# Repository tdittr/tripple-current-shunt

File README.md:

# Tripple Current Shunt

This is a small PCB project to measure current consumption and voltages in a multi battery camper van environment.

To do this it hosts three [INA219](https://www.ti.com/product/INA219) power monitors,
one [ADS1015](https://www.ti.com/product/ADS1015) four channel ADC to measure ground offsets,
one [MCP9808](https://www.microchip.com/en-us/product/MCP9808) temperature sensor and
a [M24C02](https://www.st.com/en/memories/m24c02-r.html) EEPROM to store calibration data.

## Interfaces

The board has three different interfaces. A [I2C](#i2c) digital interface for reading the measurements.
Three [Current Inputs](#current-input)
to measure the current flows into and out of the batteries. Three [Voltage Inputs](#voltage-input) to measure the ground
offset of the batteries.

### I2C

The I2C interface is wired to two JST-PH connectors with a pin-out compatible
to [Adafruits Stemma](https://learn.adafruit.com/introducing-adafruit-stemma-qt/technical-specs) connection. The
footprint also fits the connector and pin-out
of [Seedstudios Grove System](https://wiki.seeedstudio.com/Grove_System/#grove-i2c). The two connectors are wired in
parallel to allow for daisy-chaining. The power is also supplied via this connector (from rev2 onwards).

**Note on using Grove Connectors:** The 90 degree version of the grove connector seem to count their pins from right to
left - so inverse to how JST counts their pins. To use the Grove connectors you can either mount them on the backside of
the board or use the upright connectors with the clip facing to the edge of the board.

#### I2C Addresses

The six I2C slaves on the board are configured to follow a schema where the lowest two bits of the address are defined
per board. This allows usage of up to four boards with a total of 12 channels on a single bus. The individual addresses
are listed below. *xx* marks the bits set via jumpers (see screenshot below).

| Device      | Address Pattern | Board 0 | Board 1 | Board 2 | Board 3 |
|-------------|-----------------|---------|---------|---------|---------|
| MCP9808     | 0b001_10*xx*    | 0x18    | 0x19    | 0x1a    | 0x1b    |
| INA219 Ch A | 0b100_00*xx*    | 0x40    | 0x41    | 0x42    | 0x43    |
| INA219 Ch B | 0b100_01*xx*    | 0x44    | 0x45    | 0x46    | 0x47    |
| ADS1015     | 0b100_10*xx*    | 0x48    | 0x49    | 0x4a    | 0x4b    |
| INA219 Ch C | 0b100_11*xx*    | 0x4c    | 0x4d    | 0x4e    | 0x4f    |
| M24C02      | 0b101_00*xx*    | 0x50    | 0x51    | 0x52    | 0x53    |

|                                                                                                                                      |
|--------------------------------------------------------------------------------------------------------------------------------------------------------------------------------------------------------|
| There should always be one of JP1, JP2, JP3 or JP4 closed. Then close JP11 or JP12 when the matching box is filled. To select for example the address *10* for the board you would close JP3 and JP12. |

### Current Input

The current inputs are connected inline between the batteries and the consumers. They can be connected using
either [Wago 2604-1103 terminal blocks](https://www.wago.com/global/pcb-terminal-blocks-and-pluggable-connectors/pcb-terminal-block/p/2604-1103)
or a single row terminal block with 5mm pin spacing.

The board offers the option to place a [miniOTO fuse holder](https://imaxx.nl/product/minioto-holder-h7810/) in line to
protect the board and connections.

The current is then converted to a voltage using a current shunt. The different options for this are described
in ["Choosing a Shunt Resistor"](#choosing-a-shunt-resistor).

### Voltage Input

To measure the voltage offset between the board ground and the battery ground the connector used for
the [Current Input](#current-input) offers an extra connection. The input can tolerate a maximum voltage of ±20V but can
only measure about a ±5V offset. This can easily be adapted to other needs,
see [Adapting Voltage Dividers](#adapting-voltage-dividers).

## Design considerations

The board is designed to be easily adaptable to different situations. The easiest adaptions are to just leave parts out:

* Remove the fuse holders (e.g. because you already have a fuse box), and bridge that footprint
* Remove the temperature sensor and/or EEPROM to save cost
* Remove the EMI filter by not populating the capacitors and bridging the ferrite-beads

For the more complex considerations see below:

### Choosing a Shunt Resistor

**1. Choosing a footprint:** The board offers four different footprints for the shunt resistors:

* Single-Inline 4-pin through-hole
  for [Isabellenhütte PBV](https://www.isabellenhuette.de/fileadmin/user_upload/PBV.PDF) resistors
* SMD 2512 resistors
* SMD 1206 resistors
* Off-Board Shunt like [Vishay RTOP](https://www.vishay.com/product/50045/)

When using any other resistor footprint then the Single-Inline one the two jumpers next to the resistor footprints needs
to be closed. This connects the voltage sense terminals to the current terminals.

The screenshot shows the resistor footprints for channel A. R5 is for the *Single-Inline 4-pin through-hole* and R2 for
either SMD 2512 or SMD 1206. To use an external shunt do not populate any of the two. If you want to use any shunt that
is not the Single-Inline 4-pin close the two jumpers below R2.

**2. Check maximum values:** Calculate the maximum resistor value for a given current and power rating:

$R \leq \frac{P}{I^2}$

**3. Check voltage over shunt:** The INA219 can work with up to 26V but can measure a either ±40mV, ±80mV, ±160mV or
±320mV of shunt voltage. Using a lower shunt voltage will give a lower power loss on the shunt while aiming for a higher
shunt voltage increases signal-to-noise ratio.
You can calculate the voltage over the shunt by $U_{shunt}=R_{shunt} \cdot I$.

**Note:** Check whether the trace width is sufficient for your current. You can add extra solder and copper to the
traces on the bottom side to improve the current capabilities.

### Adapting Voltage Dividers

The voltage dividers for the ground offset are set to allow for ±5V input. This is achieved by building a voltage
divider between the input voltage and 5V. The output voltage can then be calculated by:

$U_{out} = \frac{5V + U_{in}}{2}$

There are however footprints to form a voltage divider between the input and ground. So it could be used to measure
another bus voltage.

**Note:** When adapting this take care to not overload the clamping diodes or the resistors in the voltage divider.

### Adapting Low Pass Filters

The current and voltage inputs host capacitors to form RC low-pass filters. The calculations for these can be found in
the schematic.

# License

Licensed under the CERN Open Hardware Licence Version 2 - Permissive.
Unless you explicitly state otherwise, any contribution intentionally submitted by you, shall be licensed as above,
without any additional terms or conditions.

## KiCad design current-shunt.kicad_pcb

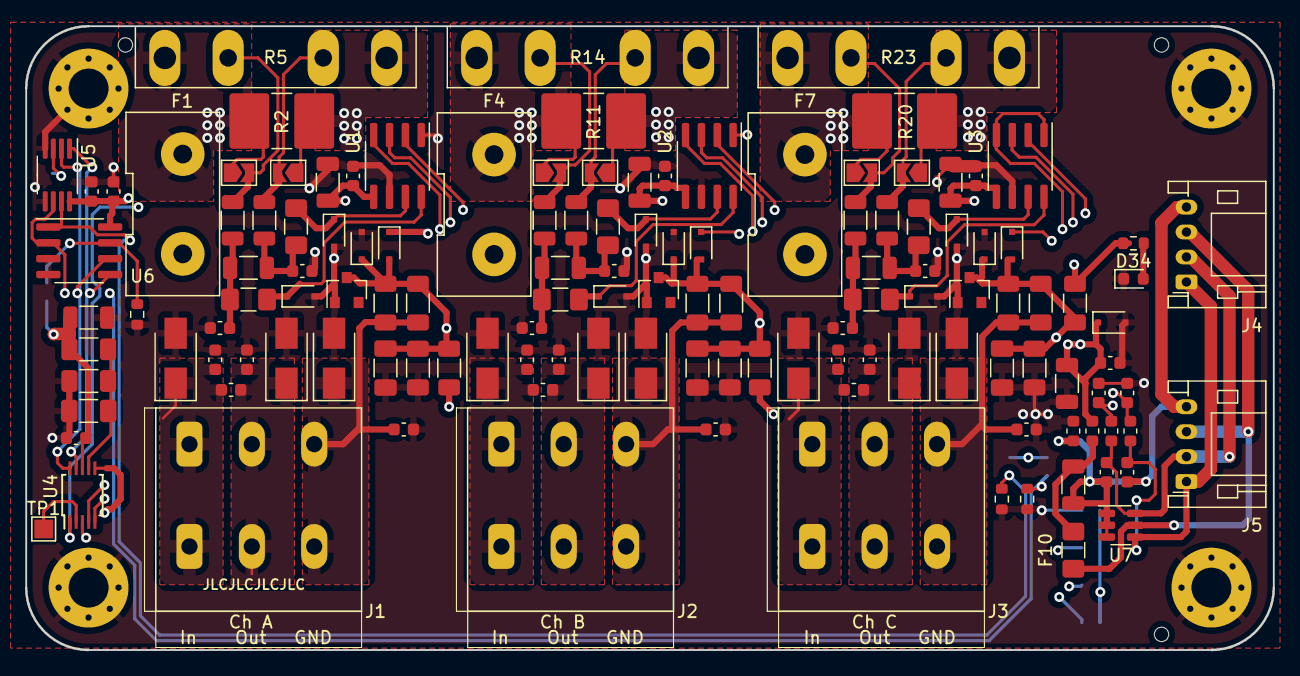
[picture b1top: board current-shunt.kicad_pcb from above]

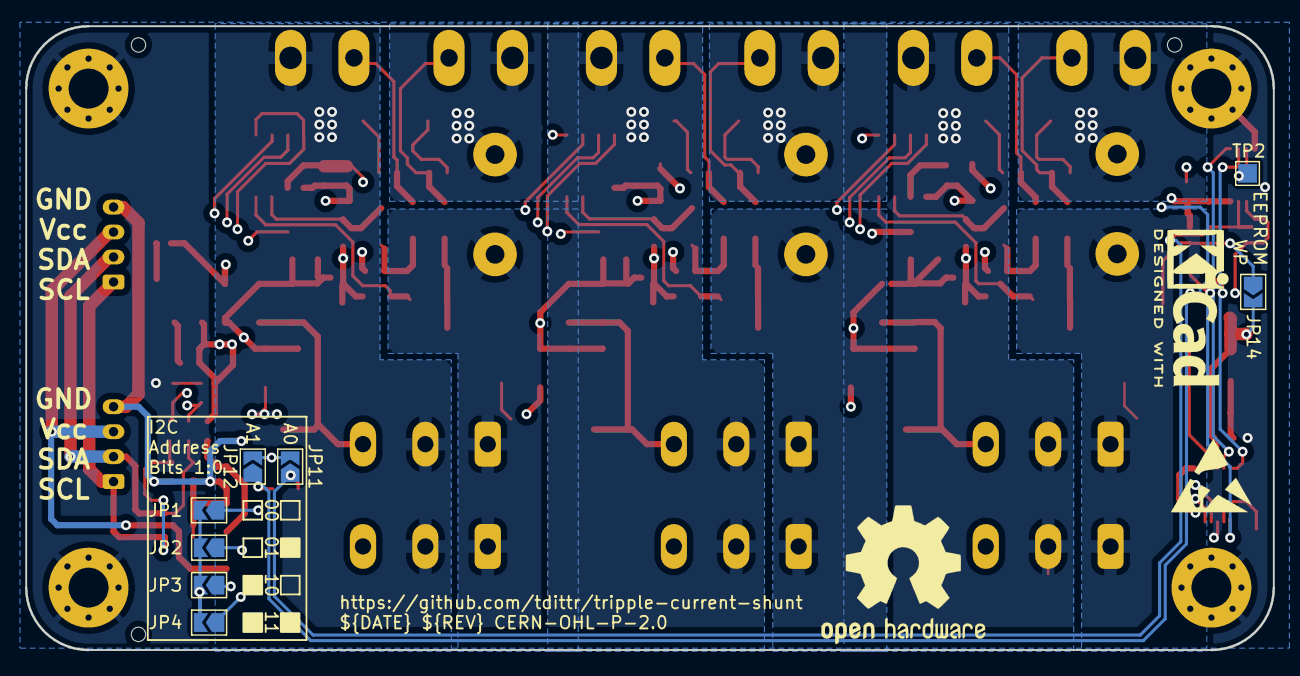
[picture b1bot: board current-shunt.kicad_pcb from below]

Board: 4 copper layers, 100.0 x 50.0 mm, 146 parts (11 on the bottom side), 50 nets.

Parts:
C1, C11, C21, C32, C37, C40: 10uF; C_1206_3216Metric
C2, C9, C10, C12, C19, C20, C22, C29, C30, C33, C34, C35, C36: 100nF; C_0603_1608Metric
C3, C4, C5, C6, C13, C14, C15, C16, C23, C24, C25, C26: 10nF; C_0603_1608Metric
C7, C17, C27, C31: 330nF; C_1206_3216Metric_Pad1.33x1.80mm_HandSolder
C8, C18, C28: 1uF; C_1206_3216Metric
C38, C39, C41, C42: 33pF; C_0603_1608Metric
D4, D5, D6, D15, D16, D17, D26, D27, D28: SMAJ20CA; D_SMA
D7, D8, D9, D10, D18, D19, D20, D21, D29, D30, D31, D32, D35: PMEG4010BEA; D_SOD-323F
D11, D22, D33: BZX84C 4V7; D_SOT-23_ANK
D34: LED; LED_0603_1608Metric
F1, F4, F7: Fuse; iMaXX-H7810
F2, F3, F5, F6, F8, F9, F10: 1206L016WR; Fuse_1206_3216Metric_Pad1.42x1.75mm_HandSolder
FB1, FB2, FB3, FB4: FerriteBead; L_0603_1608Metric
H1, H2, H3, H4: MountingHole_Pad; MountingHole_3.2mm_M3_Pad_Via
J1, J2, J3: Screw_Terminal_01x03; Wago_2604-1103
J4, J5: Conn_01x04; JST_PH_S4B-PH-K_1x04_P2.00mm_Horizontal
JP1, JP2, JP3, JP4, JP5, JP6, JP7, JP8, JP9, JP10, JP11, JP12, JP14: SolderJumper_2_Open; SolderJumper-2_P1.3mm_Open_TrianglePad1.0x1.5mm
LOGO1: Logo_Open_Hardware_Small; OSHW-Logo2_14.6x12mm_SilkScreen
LOGO2: SYM_ESD_Small; ESD-Logo_6.6x6mm_SilkScreen
LOGO3: SYM_Arrow45_XLarge; KiCad-Logo2_5mm_SilkScreen
R2, R11, R20: R; R_2816_7142Metric_Pad3.20x4.45mm_HandSolder
R3, R4, R12, R13, R21, R22: 2k; R_1206_3216Metric_Pad1.30x1.75mm_HandSolder
R5, R14, R23: R_Shunt; R_Shunt_Isabellenhuette_PBV
R6, R7, R15, R16, R24, R25: 10R; R_1206_3216Metric
R8, R17, R26, R28, R29: 1k; R_1206_3216Metric_Pad1.30x1.75mm_HandSolder
R9, R18, R27: DNP; R_1206_3216Metric_Pad1.30x1.75mm_HandSolder
R30, R31, R33: 10K; R_0603_1608Metric
R34: 1K5; R_0603_1608Metric
TP1, TP2: TestPoint; TestPoint_Pad_1.5x1.5mm
U1, U2, U3: INA219AxD; SOIC-8_3.9x4.9mm_P1.27mm
U4: ADS1015IDGS; TSSOP-10_3x3mm_P0.5mm
U5: MCP9804_MSOP; MSOP-8_3x3mm_P0.65mm
U6: M24C02-WMN; SOIC-8_3.9x4.9mm_P1.27mm
U7: SRV05-4; SOT-23-6

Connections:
+5V: C1.1, C2.1, C11.1, C12.1, C21.1, C22.1, C32.1, C33.1, C34.1, C35.1, C36.1, C37.1, D7.1 (K), D18.1 (K), D29.1 (K), D35.1 (K), FB1.1, JP2.1 (A), JP11.2 (B), JP12.2 (B), JP14.2 (B), R8.1, R17.1, R26.1, R28.1, R34.1, U1.5 (VS), U2.1 (A1), U2.5 (VS), U3.5 (VS), U4.8 (VDD), U5.8 (VDD), U6.8 (VCC)
/SCL: C39.1, FB3.1, JP4.1 (A), U1.4 (SCL), U2.4 (SCL), U3.1 (A1), U3.4 (SCL), U4.10 (SCL), U5.2 (SCL), U6.6 (SCL)
/SDA: C38.1, FB2.1, JP3.1 (A), U1.3 (SDA), U2.3 (SDA), U3.3 (SDA), U4.9 (SDA), U5.1 (SDA), U6.5 (SDA)
/gnd-level/A0: JP1.2 (B), JP2.2 (B), JP3.2 (B), JP4.2 (B), U1.2 (A0), U2.2 (A0), U3.2 (A0), U4.1 (ADDR)
/gnd-level/ALERT: TP1.1, U4.2 (ALERT/RDY)
/gnd-level/GND-A: C7.1, D7.2 (A), D8.1 (K), D11.1 (K), R3.1, R4.1, R8.2, R9.1, U4.4 (AIN0)
/gnd-level/GND-B: C17.1, D18.2 (A), D19.1 (K), D22.1 (K), R12.1, R13.1, R17.2, R18.1, U4.5 (AIN1)
/gnd-level/GND-C: C27.1, D29.2 (A), D30.1 (K), D33.1 (K), R21.1, R22.1, R26.2, R27.1, U4.6 (AIN2)
/i2c-interface/GND_e: C40.2, C41.2, C42.2, FB4.2, J4.4, J5.4, U7.1 (IO1), U7.2 (VN), U7.3 (IO2)
/i2c-interface/SCL_e: C42.1, FB3.2, J4.1, J5.1, U7.4 (IO3)
/i2c-interface/SDA_e: C41.1, FB2.2, J4.2, J5.2, U7.6 (IO4)
/i2c-interface/Vcc_e: F10.2, J4.3, J5.3, U7.5 (VP)
/shunt-a/IN+: C3.1, C4.1, D5.1 (A1), F1.1, J1.1
/shunt-a/IN+F: F1.2, JP5.1 (A), R2.1, R5.1
/shunt-a/IN-: C4.2, C5.1, D6.1 (A1), J1.2, JP6.1 (A), R2.2, R5.4
/shunt-a/IN-GND: C6.1, D4.1 (A1), J1.3, R3.2, R4.2
/shunt-b/IN+: C13.1, C14.1, D16.1 (A1), F4.1, J2.1
/shunt-b/IN+F: F4.2, JP7.1 (A), R11.1, R14.1
/shunt-b/IN-: C14.2, C15.1, D17.1 (A1), J2.2, JP8.1 (A), R11.2, R14.4
/shunt-b/IN-GND: C16.1, D15.1 (A1), J2.3, R12.2, R13.2
/shunt-c/IN+: C23.1, C24.1, D27.1 (A1), F7.1, J3.1
/shunt-c/IN+F: F7.2, JP9.1 (A), R20.1, R23.1
/shunt-c/IN-: C24.2, C25.1, D28.1 (A1), J3.2, JP10.1 (A), R20.2, R23.4
/shunt-c/IN-GND: C26.1, D26.1 (A1), J3.3, R21.2, R22.2
/temperature-sensor-eeprom/A0: JP11.1 (A), R30.1, U5.7 (A0), U6.1 (E0)
/temperature-sensor-eeprom/A1: JP12.1 (A), R31.1, U5.6 (A1), U6.2 (E1)
/temperature-sensor-eeprom/ALERT: TP2.1, U5.3 (Alert)
GND: C1.2, C2.2, C3.2, C5.2, C6.2, C7.2, C9.2, C10.2, C11.2, C12.2, C13.2, C15.2, C16.2, C17.2, C19.2, C20.2, C21.2, C22.2, C23.2, C25.2, C26.2, C27.2, C29.2, C30.2, C31.2, C32.2, C33.2, C34.2, C35.2, C36.2, C37.2, C38.2, C39.2, D4.2 (A2), D5.2 (A2), D6.2 (A2), D8.2 (A), D9.2 (A), D10.2 (A), D11.2 (A), D15.2 (A2), D16.2 (A2), D17.2 (A2), D19.2 (A), D20.2 (A), D21.2 (A), D22.2 (A), D26.2 (A2), D27.2 (A2), D28.2 (A2), D30.2 (A), D31.2 (A), D32.2 (A), D33.2 (A), D34.1 (K), D35.2 (A), FB4.1, H1.1, H2.1, H3.1, H4.1, JP1.1 (A), R9.2, R18.2, R27.2, R29.2, R30.2, R31.2, R33.2, U1.1 (A1), U1.6 (GND), U2.6 (GND), U3.6 (GND), U4.3 (GND), U5.4 (GND), U5.5 (A2), U6.3 (E2), U6.4 (VSS)
unnamed: C8.2, C9.1, F3.1, R7.2
unnamed: C8.1, C10.1, F2.1, R6.2
unnamed: C18.1, C20.1, F5.1, R15.2
unnamed: C18.2, C19.1, F6.1, R16.2
unnamed: C28.1, C30.1, F8.1, R24.2
unnamed: C28.2, C29.1, F9.1, R25.2
unnamed: C31.1, R28.2, R29.1, U4.7 (AIN3)
unnamed: C40.1, F10.1, FB1.2
unnamed: D9.1 (K), F2.2, U1.8 (IN+)
unnamed: D10.1 (K), F3.2, U1.7 (IN-)
unnamed: D20.1 (K), F5.2, U2.8 (IN+)
unnamed: D21.1 (K), F6.2, U2.7 (IN-)
unnamed: D31.1 (K), F8.2, U3.8 (IN+)
unnamed: D32.1 (K), F9.2, U3.7 (IN-)
unnamed: D34.2 (A), R34.2
unnamed: JP5.2 (B), R5.2, R6.1
unnamed: JP6.2 (B), R5.3, R7.1
unnamed: JP7.2 (B), R14.2, R15.1
unnamed: JP8.2 (B), R14.3, R16.1
unnamed: JP9.2 (B), R23.2, R24.1
unnamed: JP10.2 (B), R23.3, R25.1
unnamed: JP14.1 (A), R33.1, U6.7 (~WC)

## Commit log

2022-10-25 Squash all the commits containing Wago footprint
    This should get rid of any content containing the
    copyrighted footprint even on the board. Not
    sure if this is really needed but I want to avoid
    any problems with licensing.
    This commit squashes all these commits:
    ---
2022-10-25 Add License to repo and board
2022-10-25 Add a lot of nice to haves
    * Jumpers to bridge isolation
    * I2C pullups with jumpers for input
    * Labels on input connectors
    * Geographic reference counts
2022-10-25 Cleanup custom footprints and symbols
    This makes the names more descriptive and gets rid of unused
    symbols.
2022-10-25 Update iMaXX H7810 footprint
    Finally found a better datasheet with more measurements.
2022-10-25 Update sheetname to match new use
2022-10-25 Add LCSC order numbers to more easily order at JLCPCB
2022-10-25 Remove PCB only parts from BOM
2022-10-25 Add JLCPCB rotation offsets
2022-10-25 Add JLCPCB tooling and marking
2022-10-28 Add labels to board and update not available component
2022-11-18 Shrink board and reduce features to reduce price
    * Shrink to 100mm x 50mm
    * Remove voltage regulator and use Stemma Power instead
    * Remove isolation (is easier to add outside when needed)
    * Remove reverse indicators to save space
    * Remove I2C pullups as they are no longer needed
    * Fix A2 of EEPROM and Temperature sensor to 0 to save space
2022-11-18 Start writing README, lets see how GitHub renders LaTeX
2022-11-21 Improve I2C documentation
    * Add note about Grove Connector quirk
    * Add signal labels to board
    * Add full list of I2C addresses
2022-11-21 Switch shunt footprint
    The 2816 footprint is big enough to also mount all the smaller
    resistors down to 1206 and allows munting the bigger 2816
    resistors.
2022-11-29 Update README.md
    Fix a wrong I2C address for the EEPROM

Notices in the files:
current-shunt.kicad_pcb:
${DATE} ${REV} CERN-OHL-P-2.0
